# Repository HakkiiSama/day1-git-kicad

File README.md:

# Day 1 Git + KiCad

KiCad and Git practice project.

## Tools

- KiCad
- Git
- GitHub

## Project Purpose

This project was created to practice PCB design with KiCad and version control with Git and GitHub.

The hardware is a simple regulated power supply that converts an approximately 12 V input to a 5 V output using an L78L05 linear voltage regulator.

## Circuit Description

The circuit contains:

- A 12 V input connector
- A 1N4007 diode for input protection
- An L78L05 linear voltage regulator
- Input and output filtering capacitors
- An LED with a 620 ohm resistor for output indication
- A 5 V test point
- A 5 V output connector

The main power path is:

12 V input → protection diode → voltage regulator → regulated 5 V output

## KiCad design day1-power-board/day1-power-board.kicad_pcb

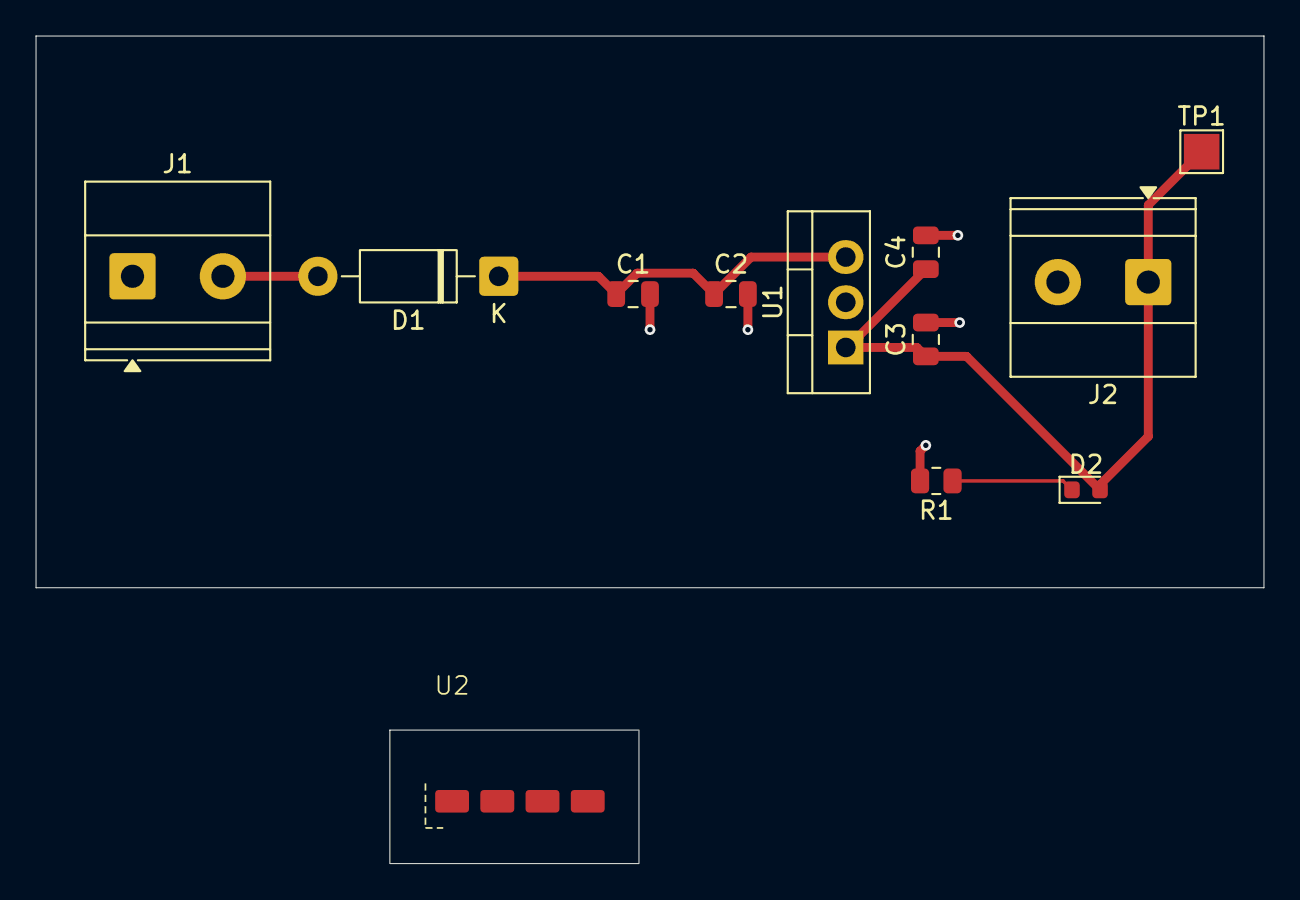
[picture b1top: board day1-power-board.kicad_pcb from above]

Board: 2 copper layers, 69.0 x 31.0 mm, 12 parts (0 on the bottom side), 5 nets.

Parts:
C1: 0.33uF; C_0805_2012Metric
C2: 10uF; C_0805_2012Metric
C3: 0.1uF; C_0805_2012Metric
C4: 33uF; C_0805_2012Metric
D1: 1N4007; D_DO-41_SOD81_P10.16mm_Horizontal
D2: LED; LED_0603_1608Metric
J1: V_IN; TerminalBlock_Phoenix_MKDS-1,5-2-5.08_1x02_P5.08mm_Horizont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
J2: V_OUT; TerminalBlock_Phoenix_MKDS-1,5-2-5.08_1x02_P5.08mm_Horizont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
R1: 620; R_0805_2012Metric
TP1: 5V_TEST; TestPoint_Pad_2.0x2.0mm
U1: L78L05_SOT89; TO-220-3_Vertical
U2: RPR-0521RS; MY_SENSOR_1x04_P2.54mm

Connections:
+5V: C3.1, C4.1, D2.2 (A), J2.1, TP1.1, U1.1 (OUT)
/12V_PROT: C1.1, C2.1, D1.1 (K), U1.3 (IN)
/12V_RAW: D1.2 (A), J1.2
GND: C1.2, C2.2, C3.2, C4.2, J1.1, J2.2, R1.2, U1.2 (GND)
unnamed: D2.1 (K), R1.1
